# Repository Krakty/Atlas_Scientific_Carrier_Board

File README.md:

# Atlas Scientific EZO Carrier Board

## Overview
A professional carrier board designed for Atlas Scientific EZO circuit boards, featuring full electrical isolation and integrated SMA connectors for reliable sensor connectivity.

Based on the [Atlas Scientific Electrically Isolated EZO Carrier Board Gen 2](https://atlas-scientific.com/carrier-boards/electrically-isolated-ezo-carrier-board-gen-2/), this design provides enhanced isolation and connectivity features for demanding applications.

### Design Improvements
This prototype incorporates several component upgrades from the reference design:
- **SI8600AC-B-ISR digital isolators** for improved signal integrity and isolation performance
- **RFM-0505S power modules** for reliable isolated power delivery
- **1206 package components** for easier hand assembly and prototype testing

## Features
- **4 EZO Circuit Slots**: Supports up to 4 Atlas Scientific EZO circuit boards simultaneously
- **Full Electrical Isolation**: Complete galvanic isolation between each EZO circuit to prevent ground loops and interference
- **Integrated SMA Connectors**: Professional-grade SMA connectors for secure and reliable probe connections
- **Modular Design**: Easy installation and removal of EZO circuits without soldering

## Supported EZO Circuits
This carrier board is compatible with the full range of Atlas Scientific EZO circuits including:
- pH
- ORP (Oxidation-Reduction Potential)
- Dissolved Oxygen
- Conductivity
- Temperature (RTD)
- Flow
- CO2
- Pressure
- Humidity
- And more...

## Technical Specifications
- **Isolation**: Full galvanic isolation between channels
  - **Digital Isolator**: SI8600AC-B-ISR (Silicon Labs) - High-speed digital isolator for I2C/UART signals (4x units)
  - **Power Isolation**: RFM-0505S - Isolated DC/DC converter module (5V to 5V, 4x units)
- **Connectors**: 
  - SMA female connectors (132289) for probe connections (4x)
  - JST XH 4-pin connector for I2C input
  - Pin headers for EZO circuit connections
- **Communication**: I2C/UART pass-through for each isolated channel
- **Power**: Isolated power supply for each EZO circuit
- **Protection**: BVSS138LT1G MOSFETs for level shifting and protection (4x)
- **Component Package**: 1206 series resistors and capacitors for easier prototype assembly and testing
  - 10kΩ pull-up resistors (10x)
  - 1MΩ resistors (8x)
  - 1µF capacitors (8x)
  - 470Ω LED resistor with power indicator

## Applications
- Water quality monitoring systems
- Hydroponics and aquaponics automation
- Industrial process control
- Environmental monitoring stations
- Research and development
- Educational laboratories

## Design Files
This repository contains:
- PCB design files (KiCad)
- Schematic diagrams
- [Bill of Materials (BOM)](Atlas_Scientific_Carrier_Board.csv) - Complete component list with quantities and specifications
- 3D models
- Manufacturing files (Gerbers)

## Safety & Compliance
- Designed with electrical safety in mind
- Full isolation prevents ground loops
- Protected against cross-channel interference
- Industrial-grade components

## License
[License information to be added]

## References & Documentation
- [Atlas Scientific Electrically Isolated EZO Carrier Board Gen 2](https://atlas-scientific.com/carrier-boards/electrically-isolated-ezo-carrier-board-gen-2/) - Original carrier board reference
- [Carrier Board Technical Datasheet (PDF)](https://files.atlas-scientific.com/electrically-isolated-ezo-carrier-board.pdf) - Detailed specifications and wiring diagrams
- [Atlas Scientific EZO Circuit Documentation](https://atlas-scientific.com/circuits/) - Complete EZO circuit specifications
- [Atlas Scientific Support](https://atlas-scientific.com/support/) - Technical support and resources

## Contact
For questions, support, or custom modifications, please open an issue in this repository.

---
*Professional carrier board solution for Atlas Scientific EZO circuits with enhanced isolation and connectivity*

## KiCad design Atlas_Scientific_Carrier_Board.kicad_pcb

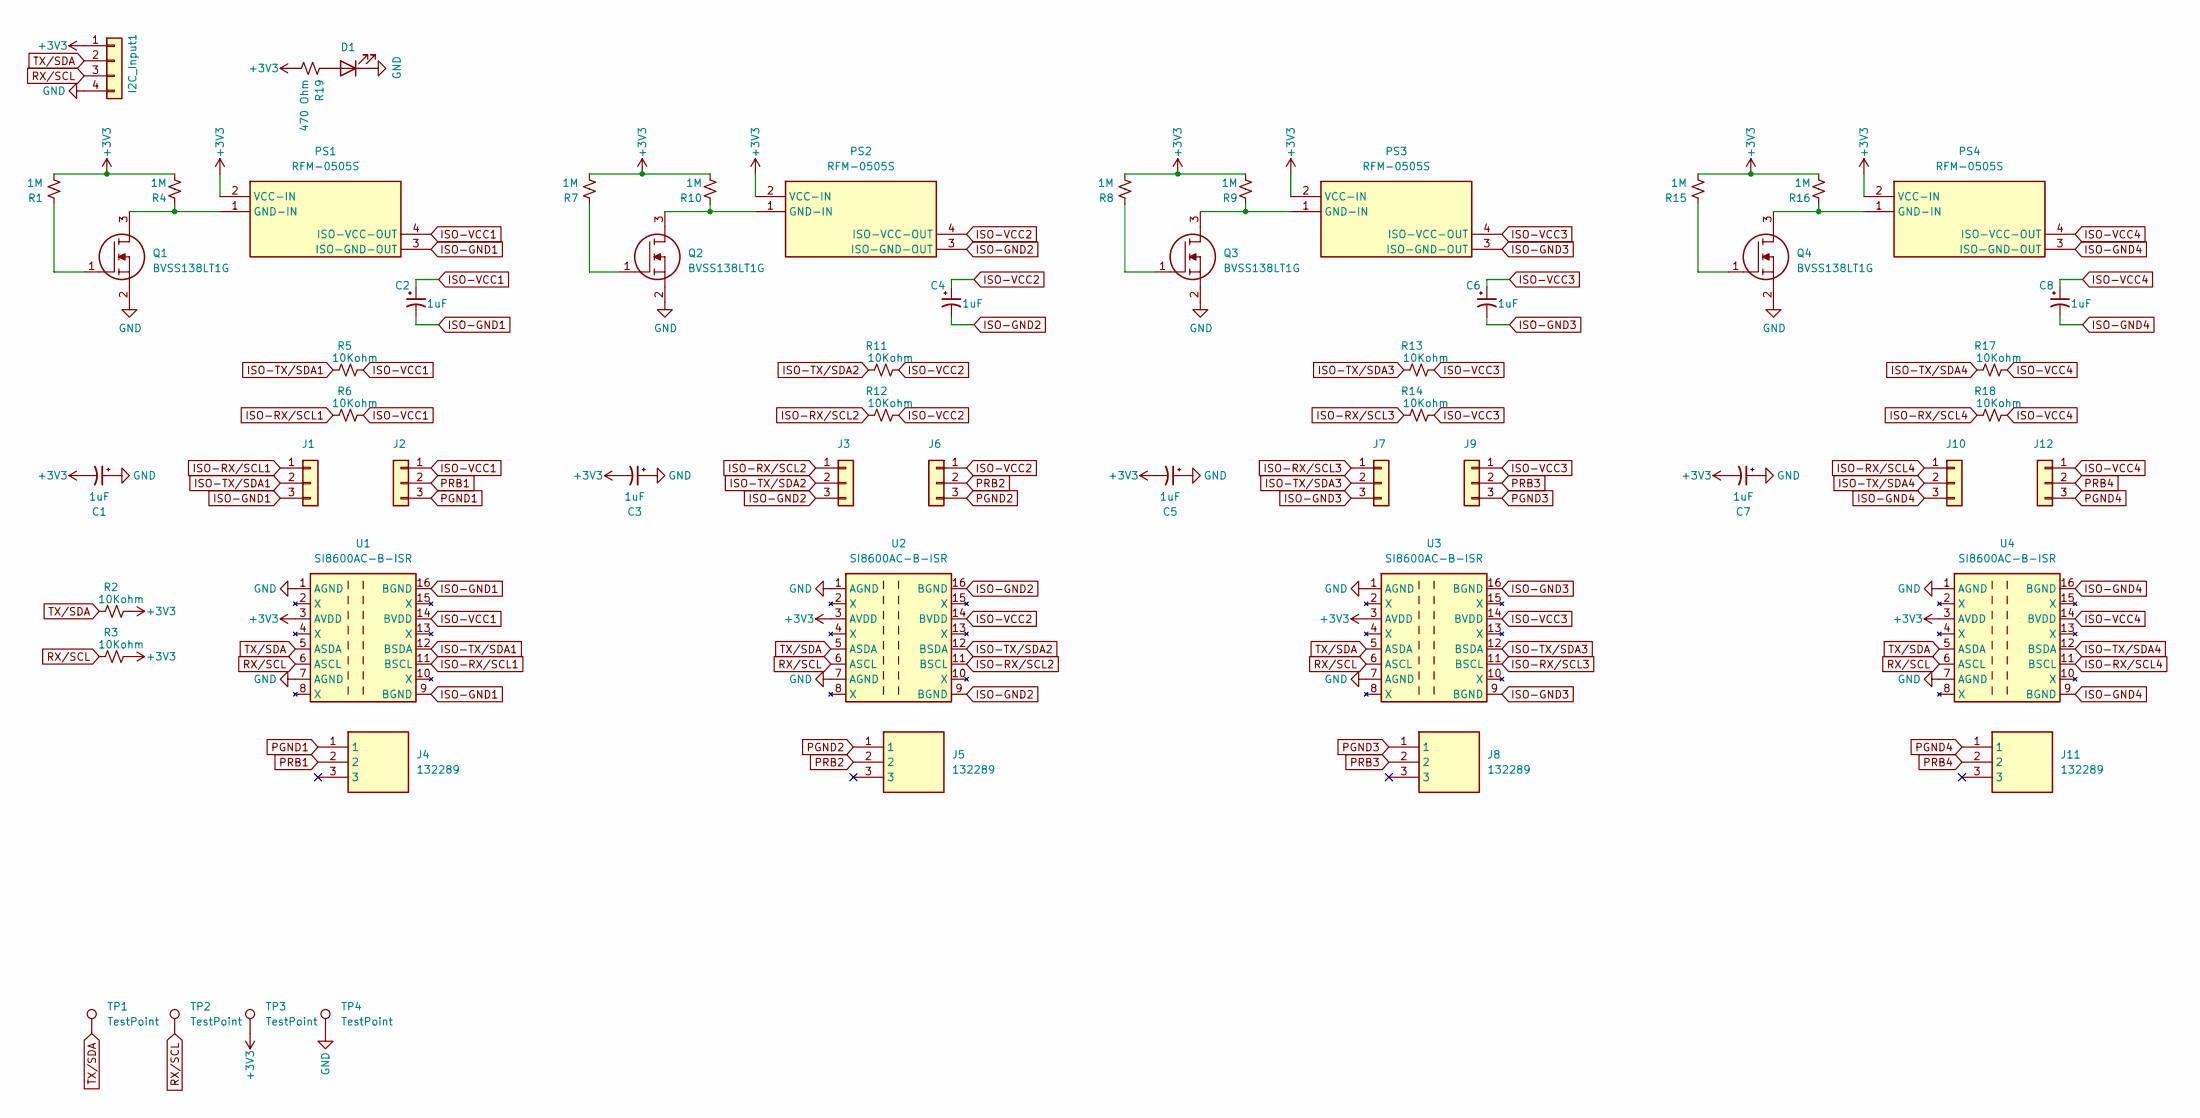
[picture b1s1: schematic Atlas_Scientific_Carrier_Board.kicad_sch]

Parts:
C1, C2, C3, C4, C5, C6, C7, C8: 1uF; C_1206_3216Metric_Pad1.33x1.80mm_HandSolder
D1: LED_1206_3216Metric_Pad1.42x1.75mm_HandSolder
I2C_Input1: JST_XH_S4B-XH-A_1x04_P2.50mm_Horizontal
J1, J2, J3, J6, J7, J9, J10, J12: Conn_01x03; PinHeader_1x03_P2.54mm_Vertical
J4, J5, J8, J11: 132289; LIB_132289; Mouser Part Number 523-132289
PS1, PS2, PS3, PS4: RFM-0505S; LIB_RFM-0505S; Mouser Part Number 919-RFM-0505S
Q1, Q2, Q3, Q4: BVSS138LT1G; SOT96P237X111-3N; Mouser Part Number 863-BVSS138LT1G
R1, R4, R7, R8, R9, R10, R15, R16: 1M; R_1206_3216Metric_Pad1.30x1.75mm_HandSolder
R2, R3, R5, R6, R11, R12, R13, R14, R17, R18: 10Kohm; R_1206_3216Metric_Pad1.30x1.75mm_HandSolder
R19: 470 Ohm; R_1206_3216Metric_Pad1.30x1.75mm_HandSolder
TP1, TP2, TP3, TP4: TestPoint; TestPoint_Loop_D2.54mm_Drill1.5mm_Beaded
U1, U2, U3, U4: SI8600AC-B-ISR; LIB_SI8600AD-B-IS; Part # SI8600AC-B-ISR

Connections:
+3V3: C1.2, C3.2, C5.2, C7.2, I2C_Input1.1, PS1.2 (VCC-IN), PS2.2 (VCC-IN), PS3.2 (VCC-IN), PS4.2 (VCC-IN), R1.2, R2.2, R3.2, R4.2, R7.2, R8.2, R9.2, R10.2, R15.2, R16.2, R19.2, TP3.1, U1.3 (AVDD), U2.3 (AVDD), U3.3 (AVDD), U4.3 (AVDD)
GND: C1.1, C3.1, C5.1, C7.1, D1.1 (K), I2C_Input1.4, Q1.2, Q2.2, Q3.2, Q4.2, TP4.1, U1.1 (AGND), U1.7 (AGND), U2.1 (AGND), U2.7 (AGND), U3.1 (AGND), U3.7 (AGND), U4.1 (AGND), U4.7 (AGND)
ISO-GND1: C2.2, J1.3, PS1.3 (ISO-GND-OUT), U1.9 (BGND), U1.16 (BGND)
ISO-GND2: C4.2, J3.3, PS2.3 (ISO-GND-OUT), U2.9 (BGND), U2.16 (BGND)
ISO-GND3: C6.2, J7.3, PS3.3 (ISO-GND-OUT), U3.9 (BGND), U3.16 (BGND)
ISO-GND4: C8.2, J10.3, PS4.3 (ISO-GND-OUT), U4.9 (BGND), U4.16 (BGND)
ISO-RX/SCL1: J1.1, R6.1, U1.11 (BSCL)
ISO-RX/SCL2: J3.1, R12.1, U2.11 (BSCL)
ISO-RX/SCL3: J7.1, R14.1, U3.11 (BSCL)
ISO-RX/SCL4: J10.1, R18.1, U4.11 (BSCL)
ISO-TX/SDA1: J1.2, R5.1, U1.12 (BSDA)
ISO-TX/SDA2: J3.2, R11.1, U2.12 (BSDA)
ISO-TX/SDA3: J7.2, R13.1, U3.12 (BSDA)
ISO-TX/SDA4: J10.2, R17.1, U4.12 (BSDA)
ISO-VCC1: C2.1, J2.1, PS1.4 (ISO-VCC-OUT), R5.2, R6.2, U1.14 (BVDD)
ISO-VCC2: C4.1, J6.1, PS2.4 (ISO-VCC-OUT), R11.2, R12.2, U2.14 (BVDD)
ISO-VCC3: C6.1, J9.1, PS3.4 (ISO-VCC-OUT), R13.2, R14.2, U3.14 (BVDD)
ISO-VCC4: C8.1, J12.1, PS4.4 (ISO-VCC-OUT), R17.2, R18.2, U4.14 (BVDD)
unnamed: D1.2 (A), R19.1
unnamed: PS1.1 (GND-IN), Q1.3, R4.1
unnamed: PS2.1 (GND-IN), Q2.3, R10.1
unnamed: PS3.1 (GND-IN), Q3.3, R9.1
unnamed: PS4.1 (GND-IN), Q4.3, R16.1
unnamed: Q1.1, R1.1
unnamed: Q2.1, R7.1
unnamed: Q3.1, R8.1
unnamed: Q4.1, R15.1
PGND1: J2.3, J4.1
PGND2: J5.1, J6.3
PGND3: J8.1, J9.3
PGND4: J11.1, J12.3
PRB1: J2.2, J4.2
PRB2: J5.2, J6.2
PRB3: J8.2, J9.2
PRB4: J11.2, J12.2
RX/SCL: I2C_Input1.3, R3.1, TP2.1, U1.6 (ASCL), U2.6 (ASCL), U3.6 (ASCL), U4.6 (ASCL)
TX/SDA: I2C_Input1.2, R2.1, TP1.1, U1.5 (ASDA), U2.5 (ASDA), U3.5 (ASDA), U4.5 (ASDA)

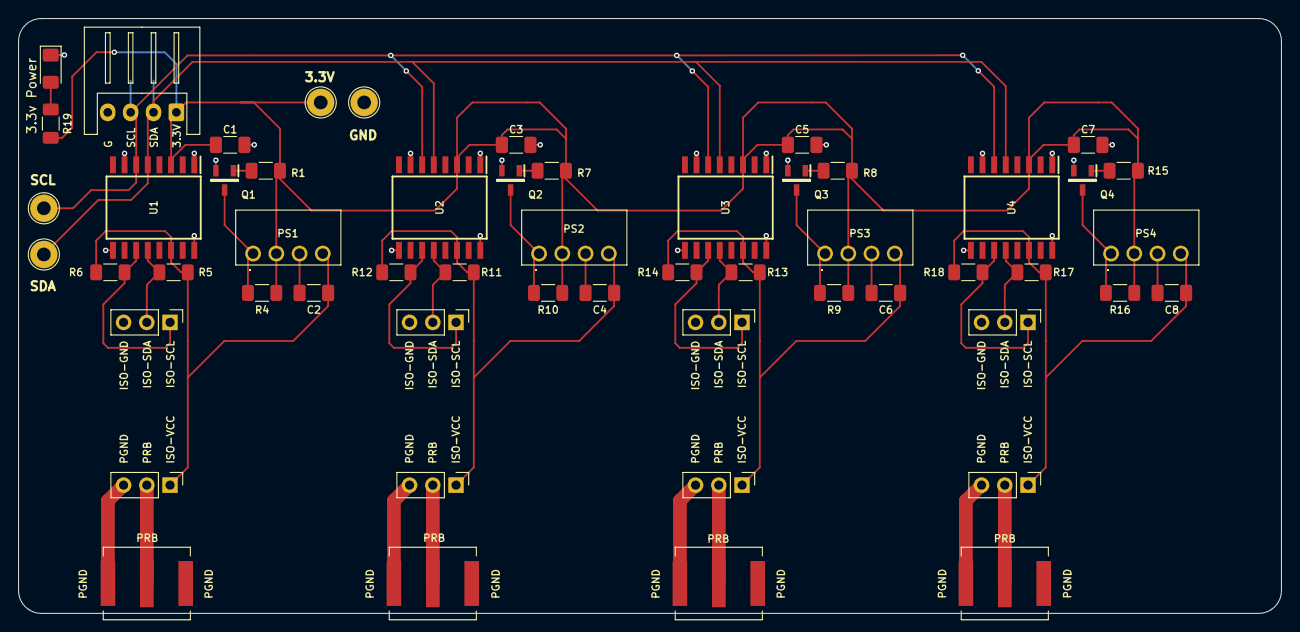
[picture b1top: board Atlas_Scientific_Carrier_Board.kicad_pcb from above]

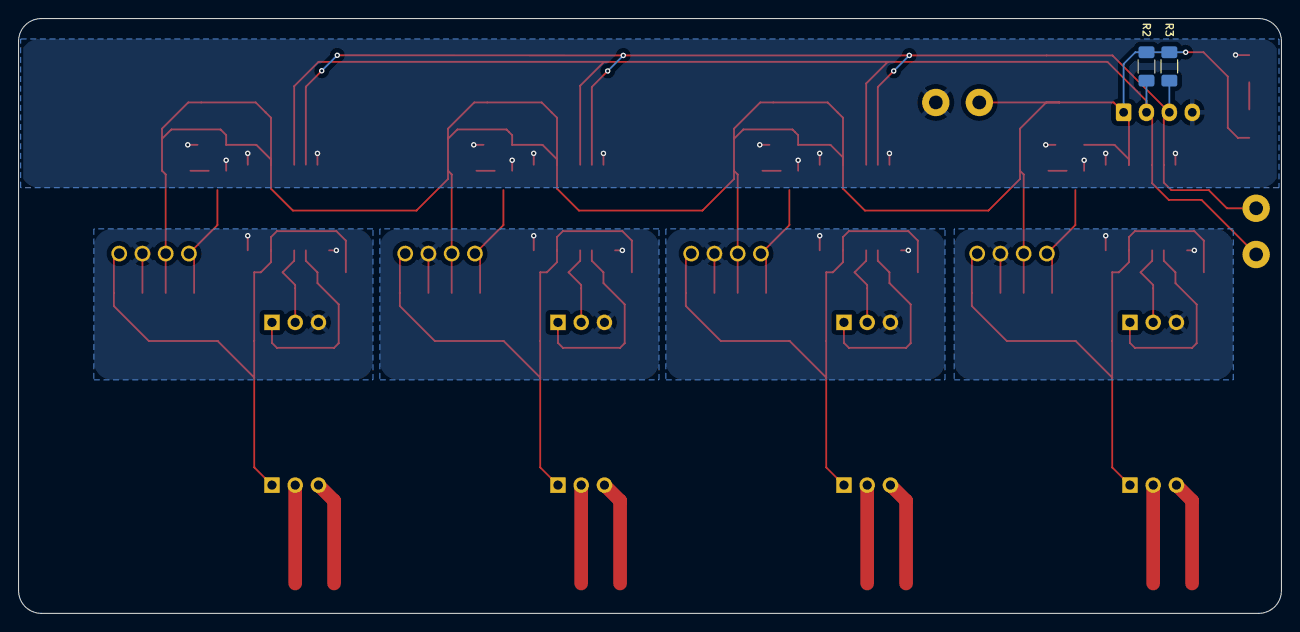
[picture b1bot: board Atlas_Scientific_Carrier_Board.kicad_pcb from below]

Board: 2 copper layers, 138.0 x 65.0 mm, 57 parts (2 on the bottom side), 37 nets.
